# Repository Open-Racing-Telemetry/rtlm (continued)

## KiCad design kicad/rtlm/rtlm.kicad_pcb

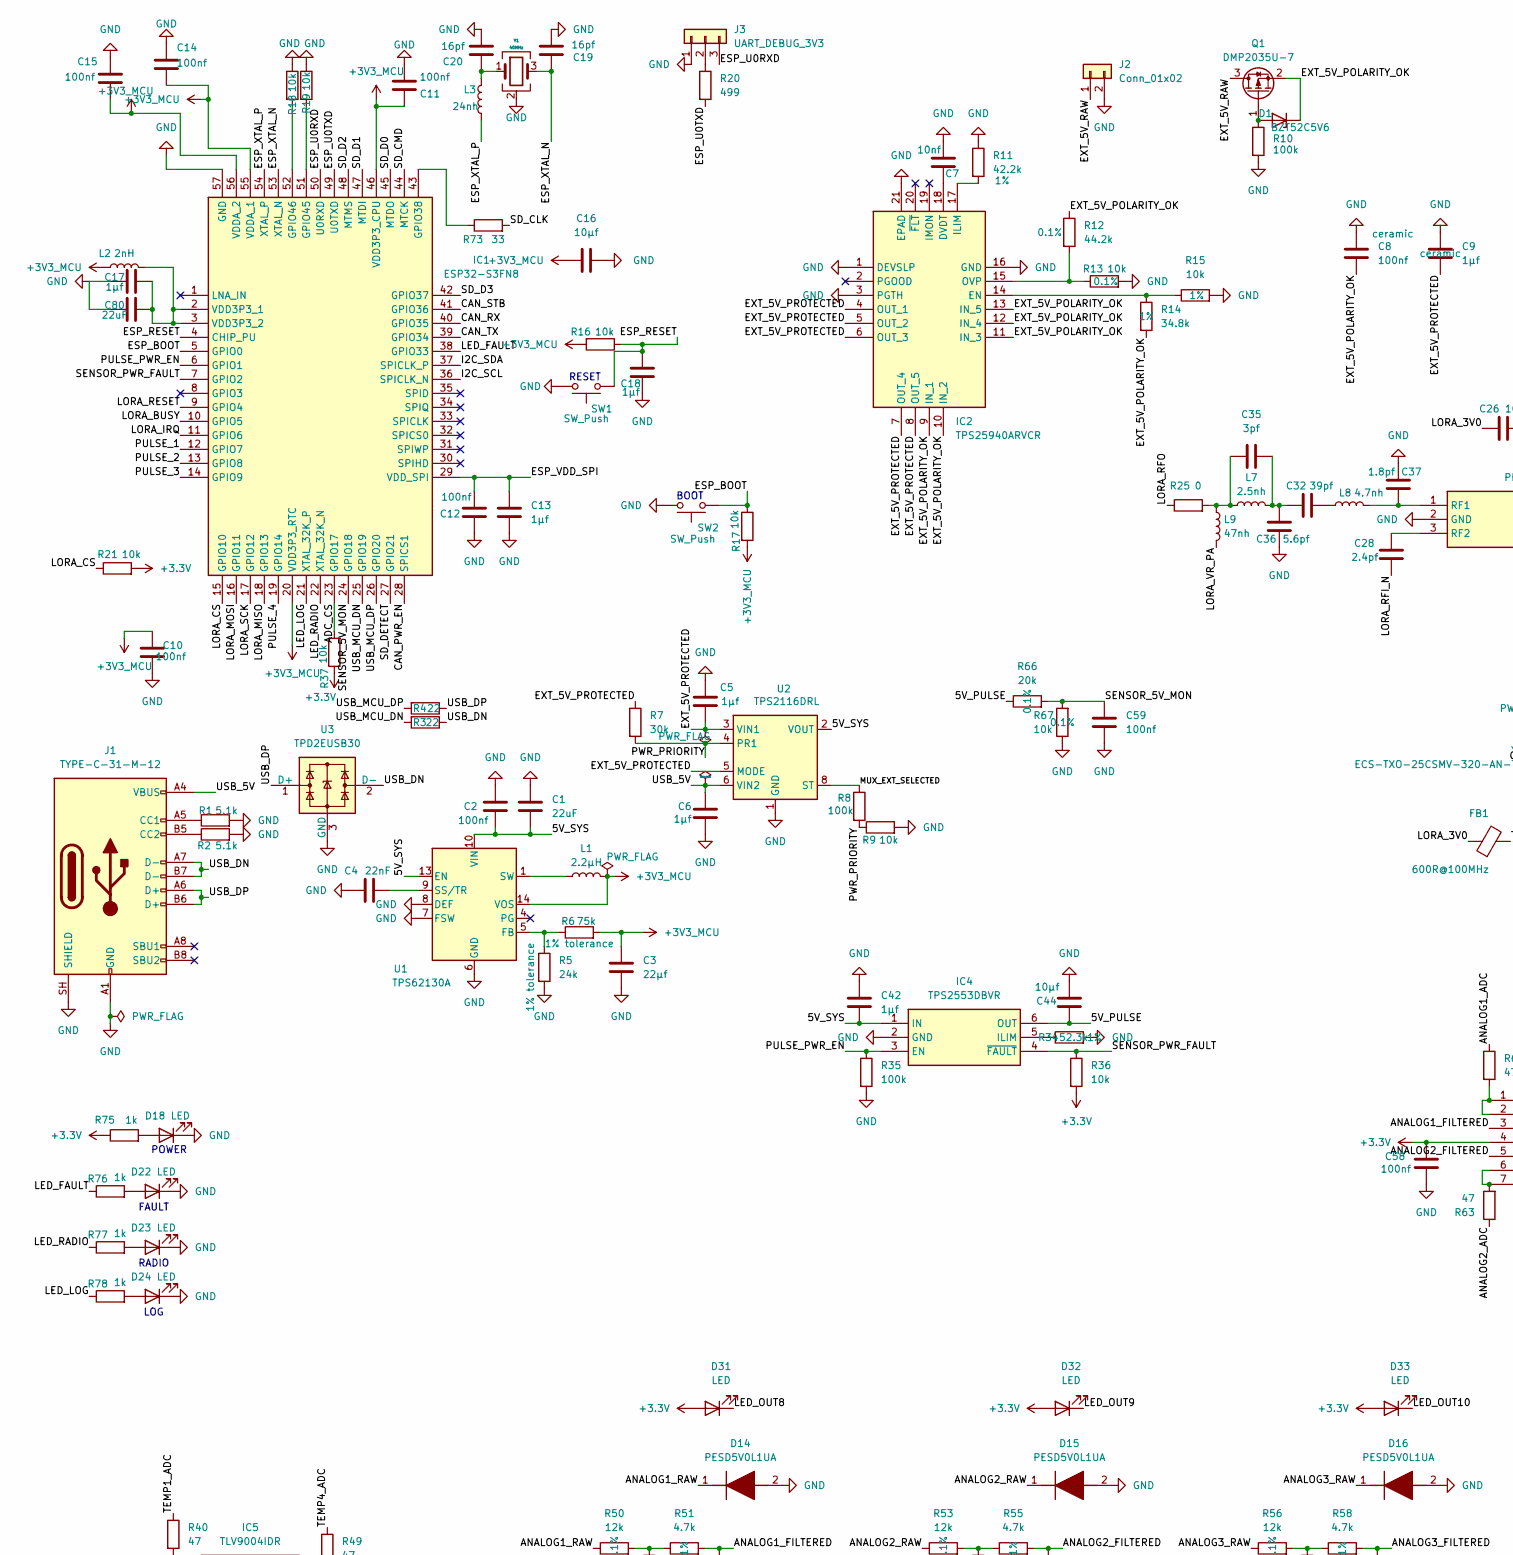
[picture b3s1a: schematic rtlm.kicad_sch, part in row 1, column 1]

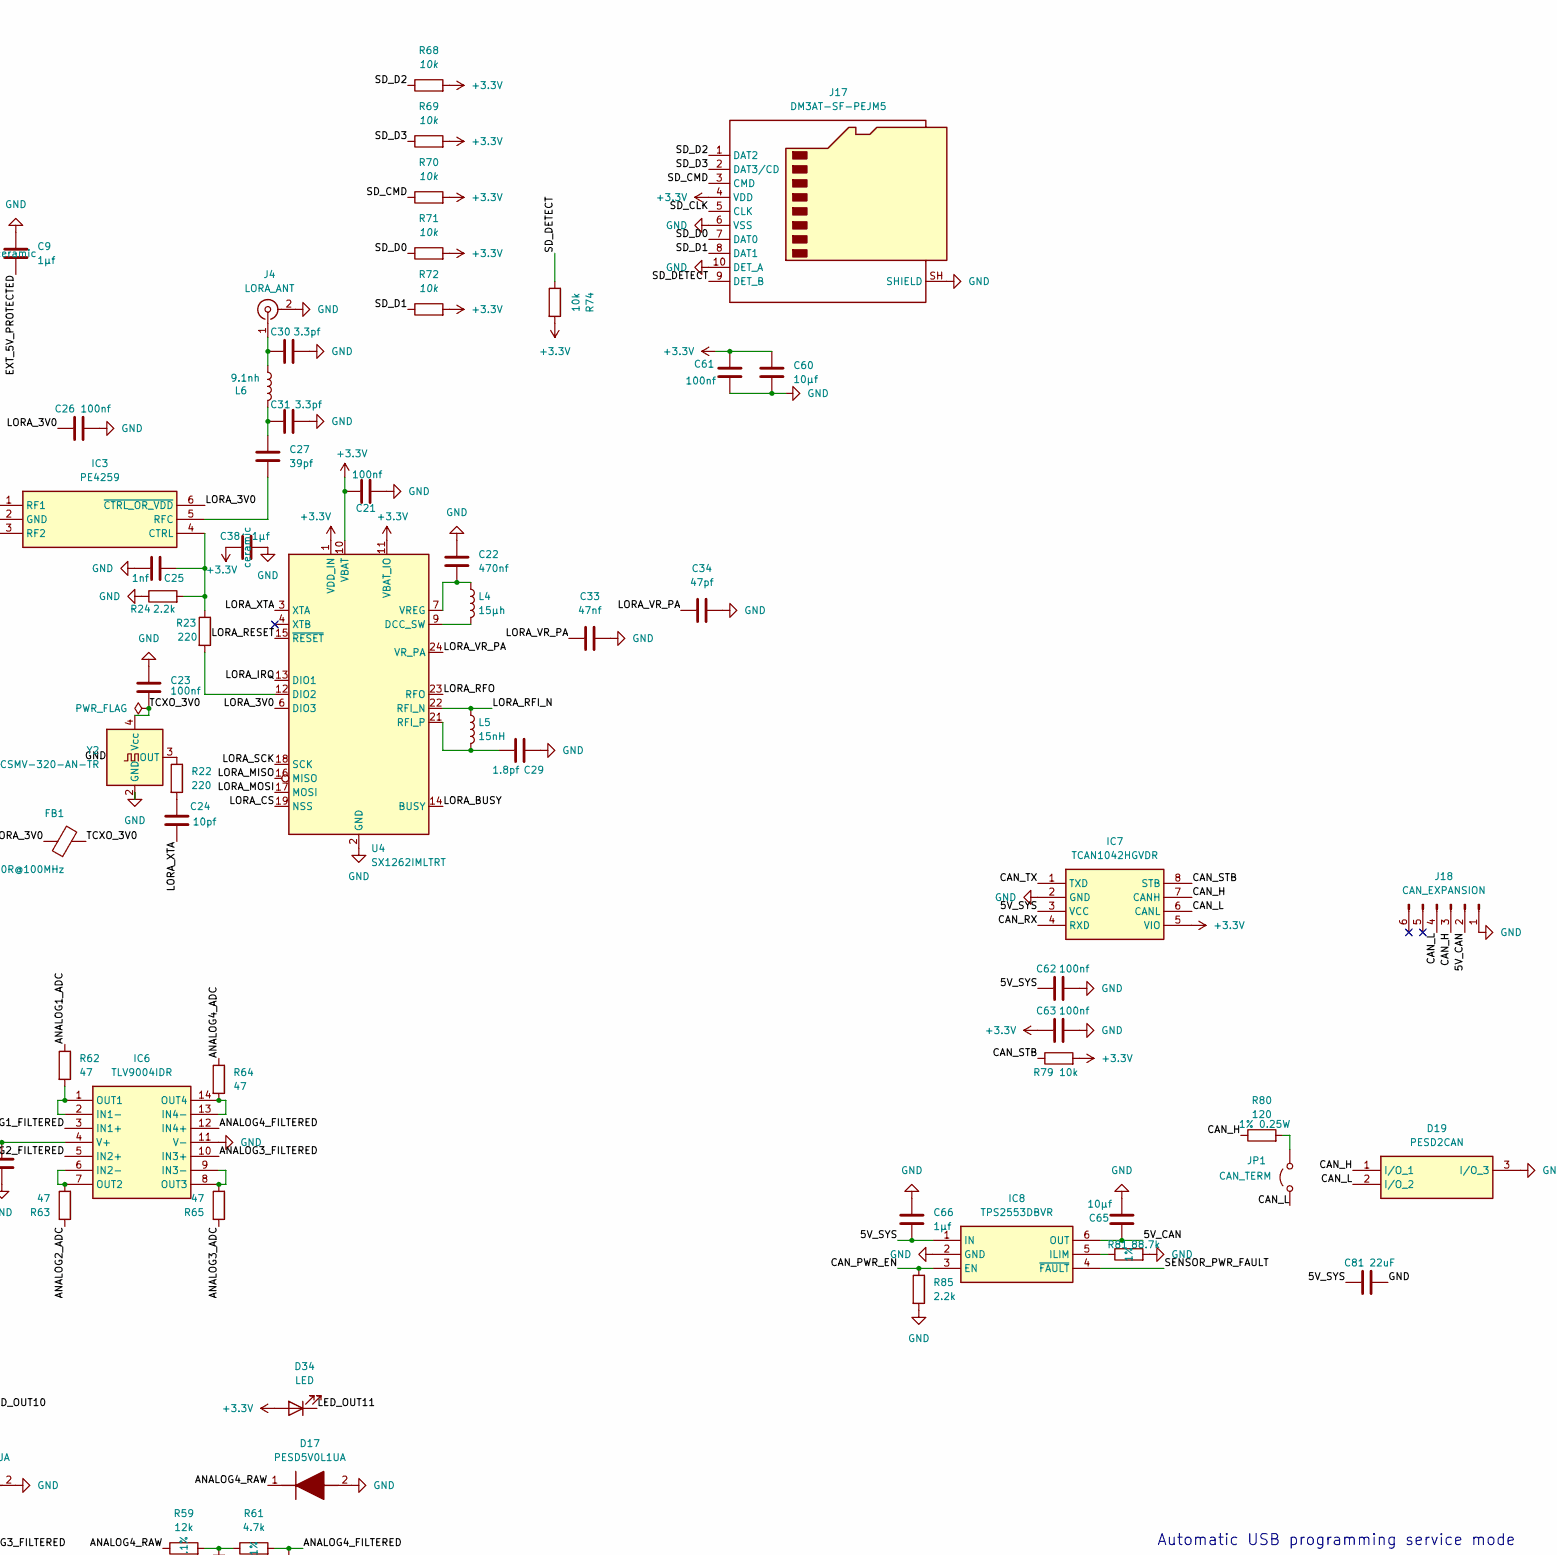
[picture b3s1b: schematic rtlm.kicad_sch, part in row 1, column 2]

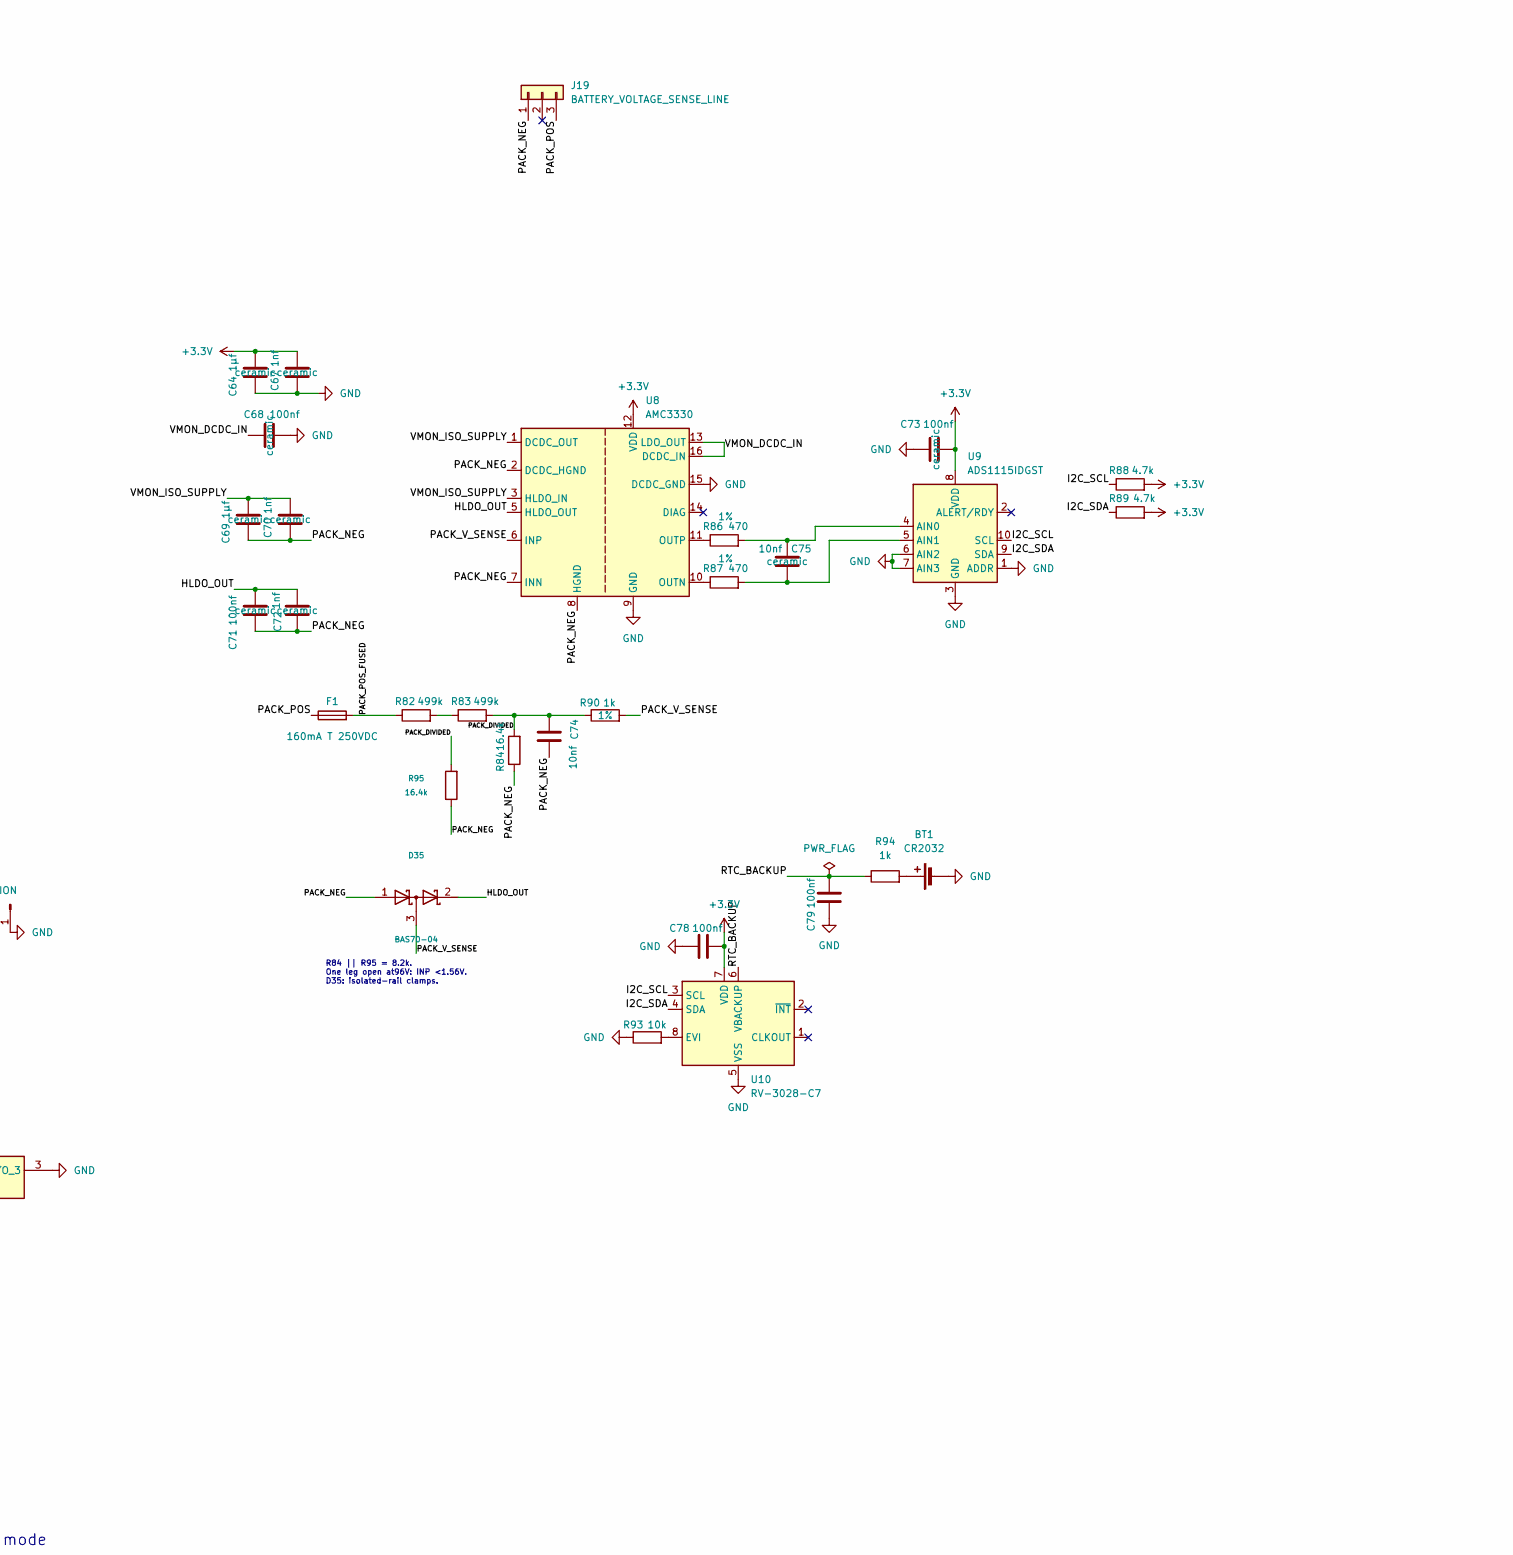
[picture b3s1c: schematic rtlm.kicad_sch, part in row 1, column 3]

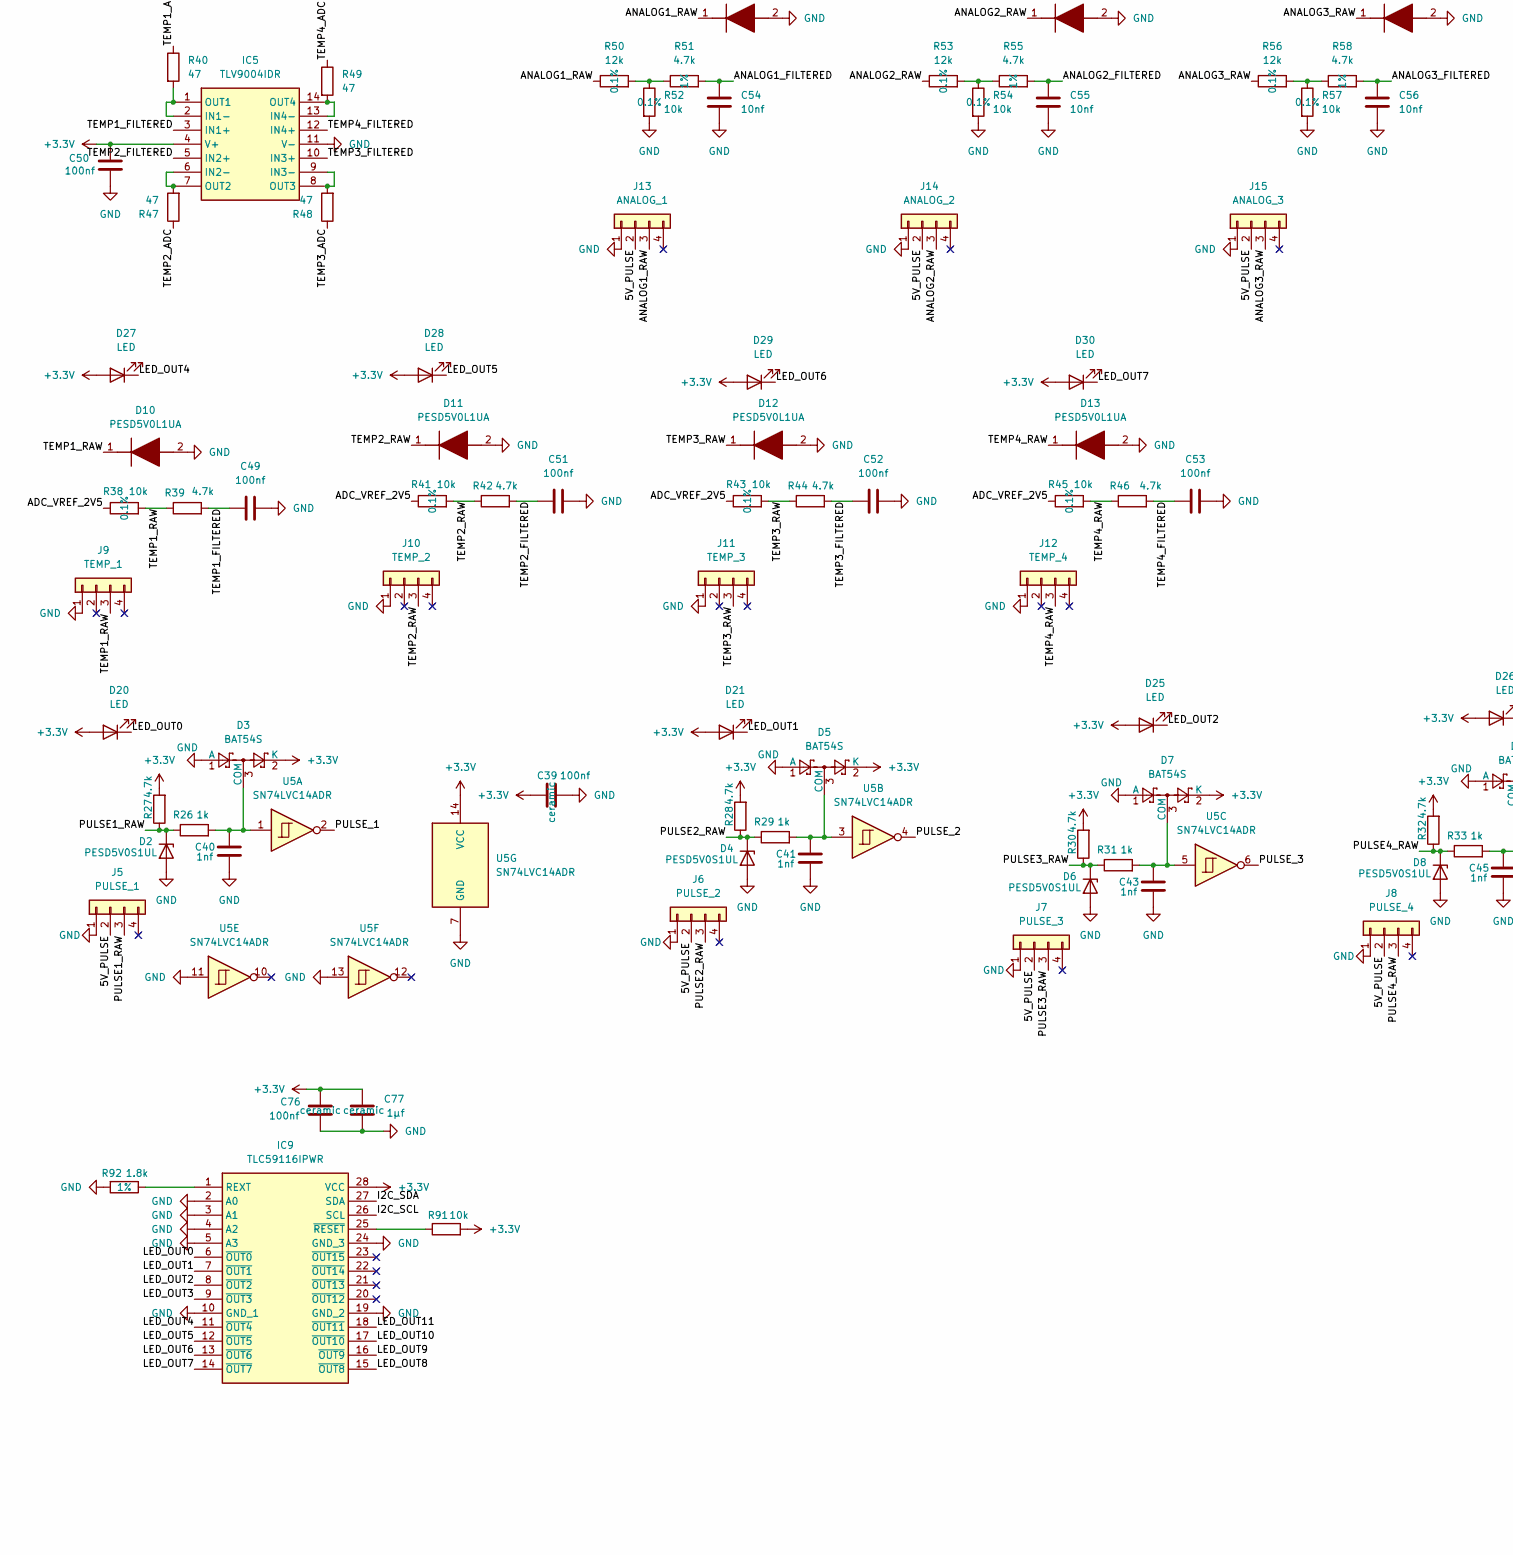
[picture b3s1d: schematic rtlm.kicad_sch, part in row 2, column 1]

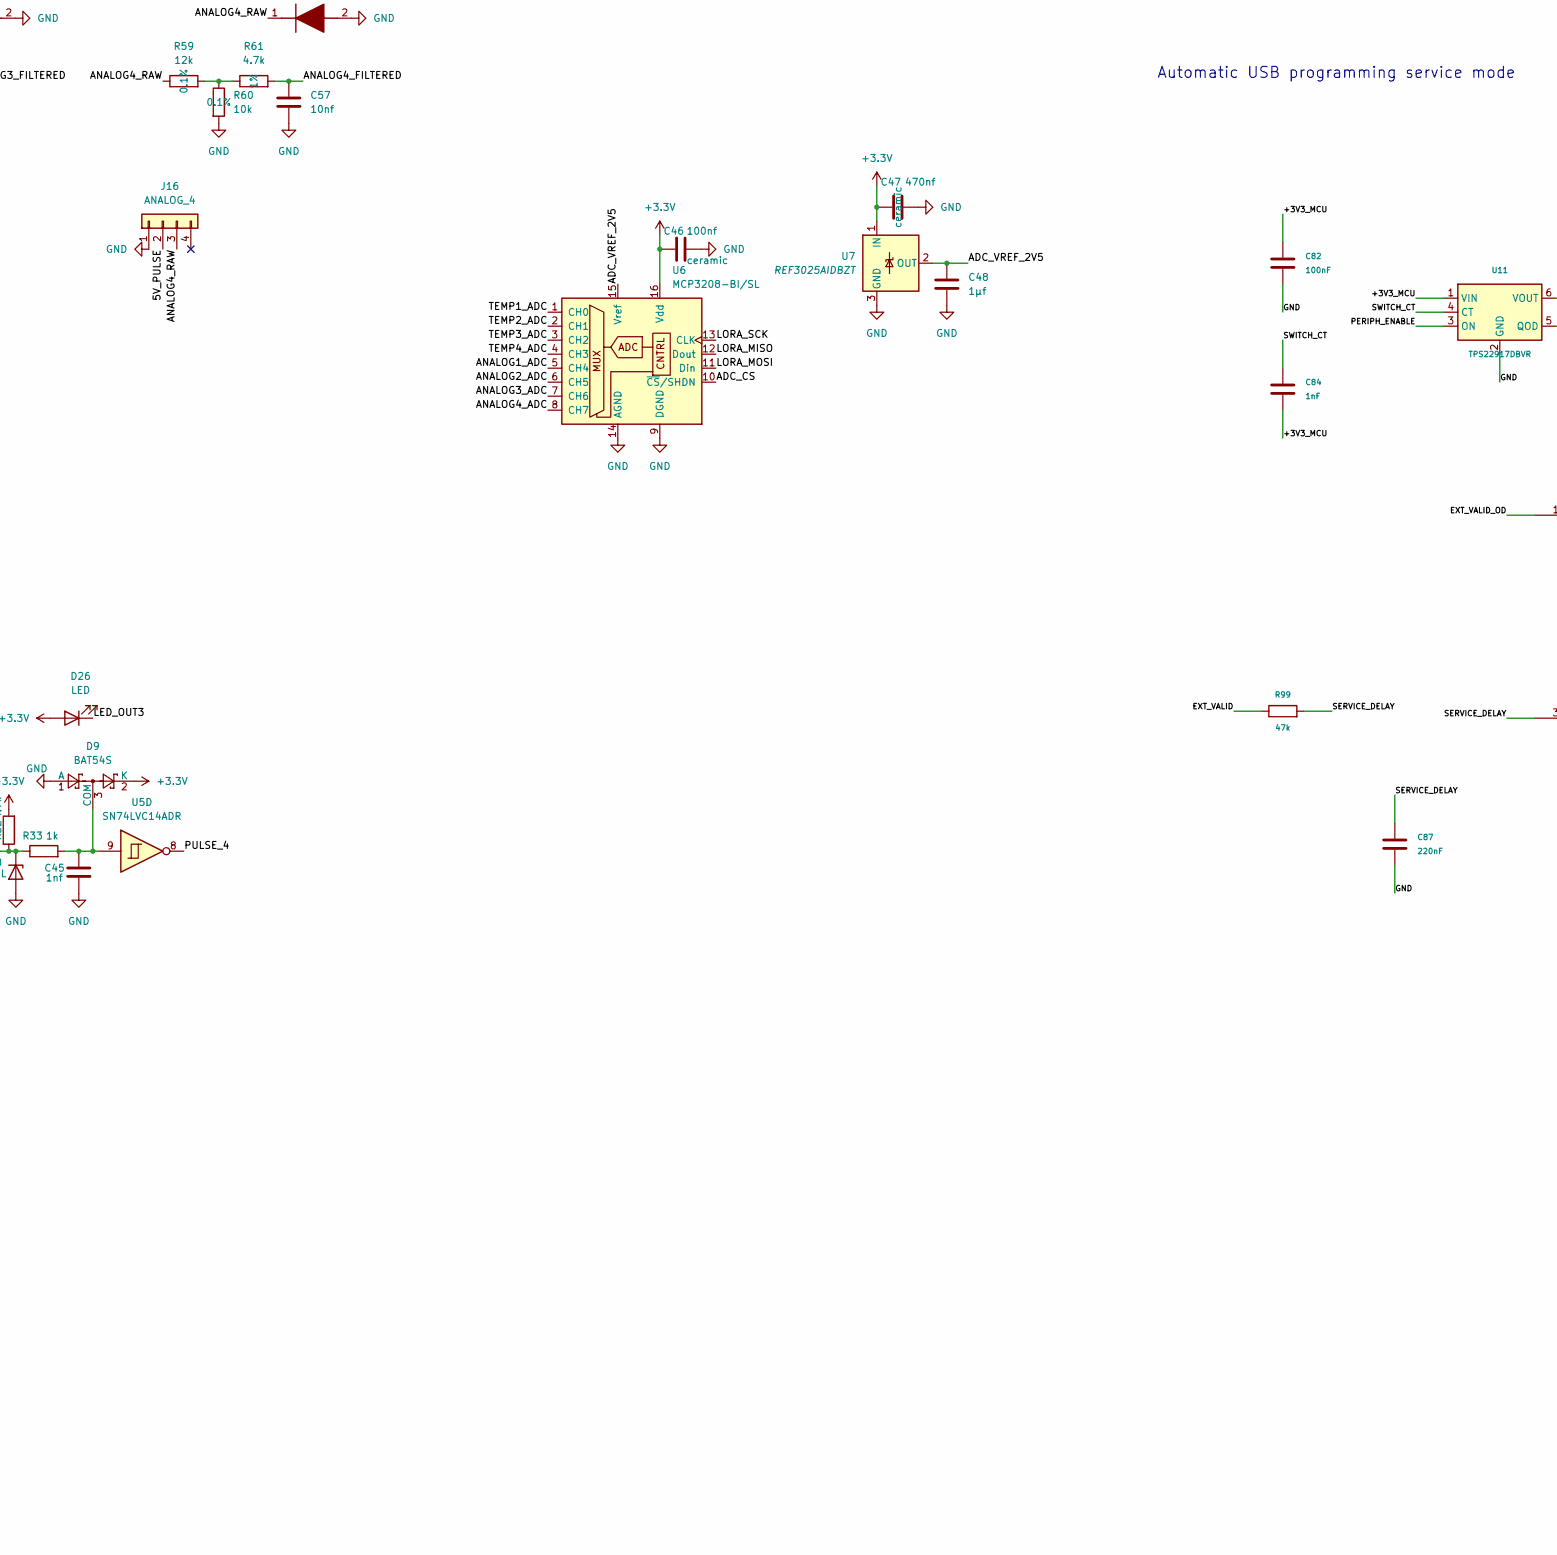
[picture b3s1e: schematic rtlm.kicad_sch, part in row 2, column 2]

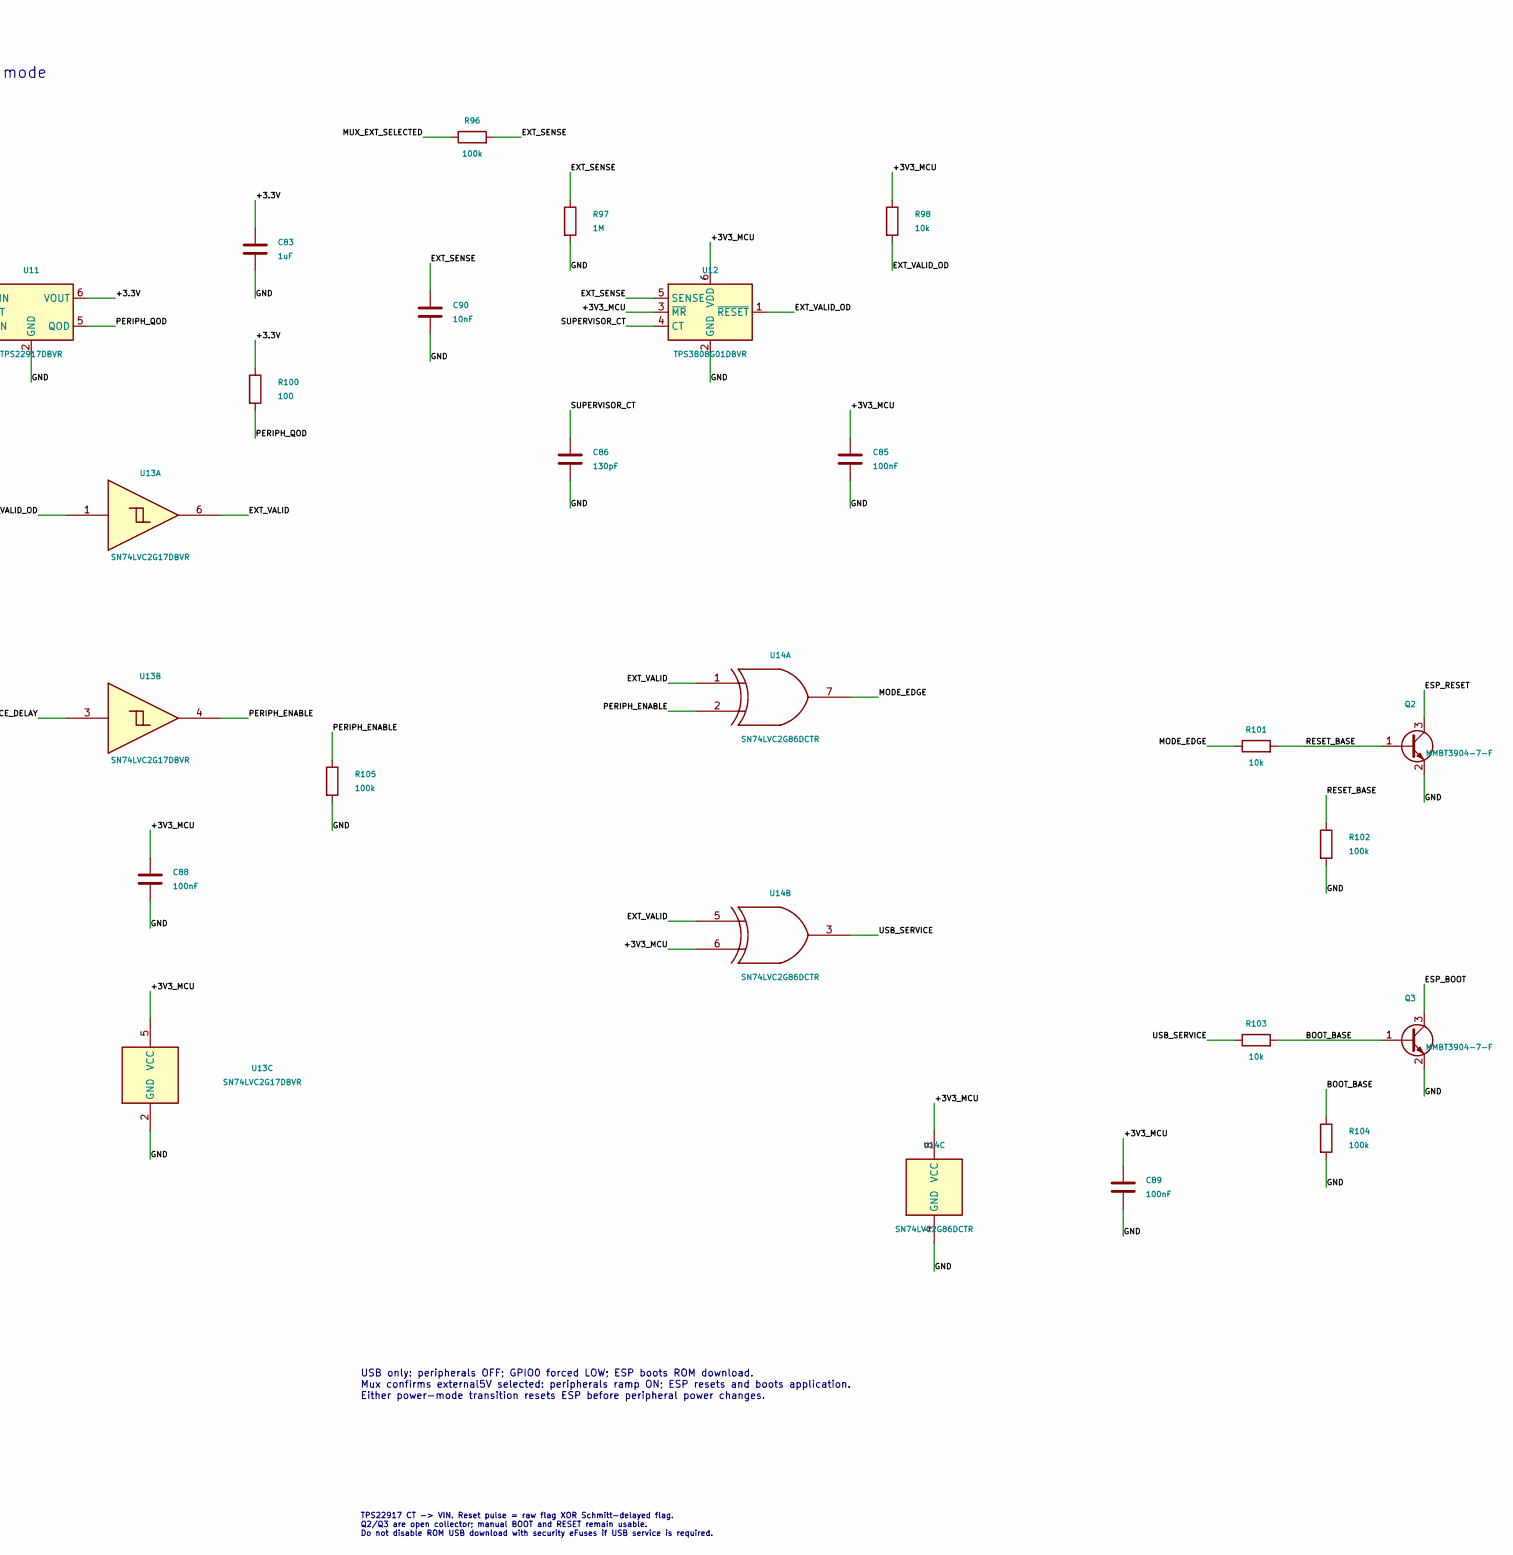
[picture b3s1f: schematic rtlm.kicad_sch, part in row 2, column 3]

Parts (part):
BT1: CR2032; BatteryHolder_Keystone_1060_1x2032; MPN 1060
C1, C80, C81: 22uF; C_0805_2012Metric; MPN GRM21BR61E226ME44L; LCSC Part Number C86816
C2, C8, C10, C11, C12, C14, C15, C39, C46, C49, C50, C51, C52, C53, C58, C59, C61, C62, C63, C68, C73, C76, C78, C79: 100nf; C_0603_1608Metric; MPN CC0603KRX7R9BB104; LCSC Part Number C14663
C3: 22µf; C_1206_3216Metric; MPN GRM31CR71A226KE15L; LCSC Part Number C91604
C4: 22nF; C_0603_1608Metric; MPN CC0603KRX7R9BB223; LCSC Part Number C106222
C5, C6, C9, C13, C17, C18, C38, C42, C48, C66, C69, C77: 1µf; C_0603_1608Metric; MPN CC0603KRX7R8BB105; LCSC Part Number C106858
C7, C54, C55, C56, C57, C75: 10nf; C_0603_1608Metric; MPN CC0603KRX7R9BB103; LCSC Part Number C100042
C16, C44, C60, C65: 10µf; C_0805_2012Metric; MPN GRM21BZ71E106KE15L; LCSC Part Number C237493
C19, C20: 16pf; C_0603_1608Metric; MPN GRM1885C1H160JA01D
C21, C23, C26: 100nf; C_0402_1005Metric; MPN CC0402KRX7R9BB104; LCSC Part Number C131394
C22: 470nf; C_0402_1005Metric; MPN CC0402KRX5R6BB474; LCSC Part Number C106255
C24: 10pf; C_0402_1005Metric; MPN GJM1555C1H100JB01D; LCSC Part Number C85874
C25: 1nf; C_0402_1005Metric; MPN CC0402JRNPO9BN102
C27, C32: 39pf; C_0402_1005Metric; MPN GJM1555C1H390JB01D
C28: 2.4pf; C_0402_1005Metric; MPN GJM1555C1H2R4BB01D
C29, C37: 1.8pf; C_0402_1005Metric; MPN GJM1555C1H1R8BB01D; LCSC Part Number C76902
C30, C31: 3.3pf; C_0402_1005Metric; MPN GJM1555C1H3R3BB01D; LCSC Part Number C76906
C33: 47nf; C_0402_1005Metric; MPN GRM155R71C473KA01D; LCSC Part Number C77012
C34: 47pf; C_0402_1005Metric; MPN GJM1555C1H470JB01D; LCSC Part Number C161322
C35: 3pf; C_0402_1005Metric; MPN GJM1555C1H3R0BB01D; LCSC Part Number C88891
C36: 5.6pf; C_0402_1005Metric; MPN GJM1555C1H5R6CB01D; LCSC Part Number C88895
C40, C41, C43, C45, C70: 1nf; C_0603_1608Metric; MPN CC0603JRNPO9BN102; LCSC Part Number C106246
C47: 470nf; C_0603_1608Metric; MPN CC0603KRX7R7BB474; LCSC Part Number C106851
C64: 1µf; C_1206_3216Metric; MPN CC1206KKX7R9BB105; LCSC Part Number C107185
C67, C72: 1nf; C_1206_3216Metric; MPN CC1206JRNPO9BN102; LCSC Part Number C113881
C71: 100nf; C_1206_3216Metric; MPN CC1206KRX7R9BB104; LCSC Part Number C82601
C74: 10nf; C_0603_1608Metric; MPN CC0603KRX7R0BB103; LCSC Part Number C107059
C82, C85, C88, C89: 100nF; C_0603_1608Metric; MPN CC0603KRX7R9BB104; LCSC Part Number C14663
C83: 1uF; C_0603_1608Metric; MPN CC0603KRX7R8BB105; LCSC Part Number C106858
C84: 1nF; C_0603_1608Metric; MPN CC0603JRNPO9BN102; LCSC Part Number C106246
C86: 130pF; C_0603_1608Metric; MPN CC0603JRNPO9BN131
C87: 220nF; C_0603_1608Metric; MPN CC0603KRX7R9BB224; LCSC Part Number C107083
C90: 10nF; C_0603_1608Metric; MPN CC0603KRX7R9BB103; LCSC Part Number C100042
D1: BZT52C5V6; D_SOD-123; MPN BZT52C5V6-7-F; LCSC Part Number C397930
D2, D4, D6, D8: PESD5V0S1UL; D_SOD-882; MPN PESD5V0S1UL,315; LCSC Part Number C85402
D3, D5, D7, D9: BAT54S; SOT-23; MPN BAT54S,215; LCSC Part Number C47546
D10, D11, D12, D13, D14, D15, D16, D17: PESD5V0L1UA; D_SOD-323; Manufacturer_Part_Number PESD5V0L1UA; Mouser Part Number N/A
D18, D20, D21, D22, D23, D24, D25, D26, D27, D28, D29, D30, D31, D32, D33, D34: LED; LED_0603_1608Metric; MPN APT1608SGC; LCSC Part Number C5875754
D19: PESD2CAN; SOT-23; Manufacturer_Part_Number PESD2CAN; LCSC Part Number C284078
D35: BAS70-04; SOT-23; MPN BAS70-04,215
F1: 160mA T 250VDC; UMT-H; MPN 3403.0266.23; LCSC Part Number C3159235
FB1: 600R@100MHz; L_0603_1608Metric; MPN BLM18AG601SN1D; LCSC Part Number C19330
IC1: ESP32-S3FN8; ESP32_S3_QFN56_EP_Windowed; Manufacturer_Part_Number ESP32-S3FN8; Mouser Part Number 356-ESP32-S3FN8
IC2: TPS25940ARVCR; Texas_RVC0020A_WQFN-20-1EP_3x4mm_P0.5mm_EP1.6x2.6mm; Manufacturer_Part_Number TPS25940ARVCR; Mouser Part Number 595-TPS25940ARVCR
IC3: PE4259; SOT65P210X110-6N; Manufacturer_Part_Number PE4259-63; Mouser Part Number N/A
IC4, IC8: TPS2553DBVR; SOT-23-6; Manufacturer_Part_Number TPS2553DBVR; Mouser Part Number 595-TPS2553DBVR
IC5, IC6: TLV9004IDR; SOIC127P600X175-14N; Manufacturer_Part_Number TLV9004IDR; Mouser Part Number 595-TLV9004IDR
IC7: TCAN1042HGVDR; SOIC-8_3.9x4.9mm_P1.27mm; Manufacturer_Part_Number TCAN1042HGVDR; Mouser Part Number 595-TCAN1042HGVDR
IC9: TLC59116IPWR; SOP65P640X120-28N; Manufacturer_Part_Number TLC59116IPWR; Mouser Part Number 595-TLC59116IPWR
J1: TYPE-C-31-M-12; USB_C_HRO_TYPE_C_31_M_12_OEM_20201208; MPN TYPE-C-31-M-12; LCSC Part Number C165948
J2: Conn_01x02; Molex_Micro-Fit_3.0_43650-0200_1x02_P3.00mm_Horizontal; MPN 436500200; LCSC Part Number C192562
J3: UART_DEBUG_3V3; PinHeader_1x03_P2.54mm_Vertical; MPN TSW-103-07-G-S; LCSC Part Number C3335811
J4: LORA_ANT; U.FL_Hirose_U.FL-R-SMT-1_Vertical; MPN U.FL-R-SMT-1(10); LCSC Part Number C88373
J5: PULSE_1; Molex_Micro-Fit_3.0_43045-0400_2x02_P3.00mm_Horizontal; MPN 430450400; LCSC Part Number C122413
J6: PULSE_2; Molex_Micro-Fit_3.0_43045-0400_2x02_P3.00mm_Horizontal; MPN 430450400; LCSC Part Number C122413
J7: PULSE_3; Molex_Micro-Fit_3.0_43045-0400_2x02_P3.00mm_Horizontal; MPN 430450400; LCSC Part Number C122413
J8: PULSE_4; Molex_Micro-Fit_3.0_43045-0400_2x02_P3.00mm_Horizontal; MPN 430450400; LCSC Part Number C122413
J9: TEMP_1; Molex_Micro-Fit_3.0_43045-0400_2x02_P3.00mm_Horizontal; MPN 430450400; LCSC Part Number C122413
J10: TEMP_2; Molex_Micro-Fit_3.0_43045-0400_2x02_P3.00mm_Horizontal; MPN 430450400; LCSC Part Number C122413
J11: TEMP_3; Molex_Micro-Fit_3.0_43045-0400_2x02_P3.00mm_Horizontal; MPN 430450400; LCSC Part Number C122413
J12: TEMP_4; Molex_Micro-Fit_3.0_43045-0400_2x02_P3.00mm_Horizontal; MPN 430450400; LCSC Part Number C122413
J13: ANALOG_1; Molex_Micro-Fit_3.0_43045-0400_2x02_P3.00mm_Horizontal; MPN 430450400; LCSC Part Number C122413
J14: ANALOG_2; Molex_Micro-Fit_3.0_43045-0400_2x02_P3.00mm_Horizontal; MPN 430450400; LCSC Part Number C122413
J15: ANALOG_3; Molex_Micro-Fit_3.0_43045-0400_2x02_P3.00mm_Horizontal; MPN 430450400; LCSC Part Number C122413
J16: ANALOG_4; Molex_Micro-Fit_3.0_43045-0400_2x02_P3.00mm_Horizontal; MPN 430450400; LCSC Part Number C122413
J17: DM3AT-SF-PEJM5; microSD_HC_Hirose_DM3AT-SF-PEJM5; MPN DM3AT-SF-PEJM5(40); LCSC Part Number C597971
J18: CAN_EXPANSION; Molex_Micro-Fit_3.0_43045-0600_2x03_P3.00mm_Horizontal; MPN 430450600; LCSC Part Number C127367
J19: BATTERY_VOLTAGE_SENSE_LINE; Molex_Micro-Fit_3.0_43650-0300_1x03_P3.00mm_Horizontal; MPN 436500300; LCSC Part Number C503478
JP1: CAN_TERM; PinHeader_1x02_P2.54mm_Vertical; MPN TSW-102-07-G-S; LCSC Part Number C7402729
L1: 2.2µH; L_Coilcraft_XxL4020; MPN XAL4020-222MEC; LCSC Part Number C3151182
L2: 2nH; L_0402_1005Metric; MPN 0402HP-2N0XJRW
L3: 24nh; L_0402_1005Metric; MPN 0402HP-24NXJRW
L4: 15µh; L_0805_2012Metric; MPN MLZ2012M150WT000; LCSC Part Number C383402
L5: 15nH; L_0402_1005Metric; MPN LQW15AN15NH00D; LCSC Part Number C91621
L6: 9.1nh; L_0402_1005Metric; MPN LQW15AN9N1H00D
L7: 2.5nh; L_0402_1005Metric; MPN LQW15AN2N5C00D; LCSC Part Number C703121
L8: 4.7nh; L_0402_1005Metric; MPN LQW15AN4N7C00D; LCSC Part Number C167480
L9: 47nh; L_0402_1005Metric; MPN 0402HP-47NXJRW
Q1: DMP2035U-7; SOT-23; MPN DMP2035U-7; LCSC Part Number C110499
Q2, Q3: MMBT3904-7-F; SOT-23; MPN MMBT3904-7-F; LCSC Part Number C94514
R1, R2: 5.1k; R_0603_1608Metric; MPN RC0603FR-075K1L; LCSC Part Number C105580
R3, R4: 22; R_0603_1608Metric; MPN RC0603FR-0722RL; LCSC Part Number C107701
R5: 24k; R_0603_1608Metric; MPN RC0603FR-0724KL; LCSC Part Number C137760
R6: 75k; R_0603_1608Metric; MPN RC0603FR-0775KL; LCSC Part Number C114636
R7: 30k; R_0603_1608Metric; MPN RC0603FR-0730KL; LCSC Part Number C100001
R8, R10, R35, R96, R102, R104, R105: 100k; R_0603_1608Metric; MPN RC0603FR-07100KL; LCSC Part Number C14675
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
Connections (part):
+3.3V: C21.1, C38.1, C39.1, C46.1, C47.1, C50.1, C58.1, C60.1, C61.1, C63.1, C64.2, C67.2, C73.2, C76.1, C77.1, C78.2, C83.1, D3.2 (K), D5.2 (K), D7.2 (K), D9.2 (K), D20.2 (A), D21.2 (A), D25.2 (A), D26.2 (A), D27.2 (A), D28.2 (A), D29.2 (A), D30.2 (A), D31.2 (A), D32.2 (A), D33.2 (A), D34.2 (A), IC5.4 (V+), IC6.4 (V+), IC7.5 (VIO), IC9.28 (VCC), J17.4 (VDD), R21.2, R27.2, R28.2, R30.2, R32.2, R36.2, R37.1, R68.2, R69.2, R70.2, R71.2, R72.2, R74.2, R75.1, R79.2, R88.2, R89.2, R91.2, R100.1, U4.1 (VDD_IN), U4.10 (VBAT), U4.11 (VBAT_IO), U5.14 (VCC), U6.16 (Vdd), U7.1 (IN), U8.12 (VDD), U9.8 (VDD), U10.7 (VDD), U11.6 (VOUT)
+3V3_MCU: C3.1, C10.2, C11.2, C14.2, C15.2, C16.1, C82.1, C84.2, C85.1, C88.1, C89.1, IC1.20 (VDD3P3_RTC), IC1.46 (VDD3P3_CPU), IC1.55 (VDDA_1), IC1.56 (VDDA_2), L1.2, L2.1, R6.2, R16.2, R17.2, R98.1, U1.14 (VOS), U11.1 (VIN), U12.3 (~MR), U12.6 (VDD), U13.5 (VCC), U14.6, U14.8 (VCC)
/5V_CAN: C65.2, IC8.6 (OUT), J18.2
/5V_PULSE: C44.2, IC4.6 (OUT), J5.2, J6.2, J7.2, J8.2, J13.2, J14.2, J15.2, J16.2, R66.1
/5V_SYS: C1.2, C2.2, C42.2, C62.1, C66.2, C81.1, IC4.1 (IN), IC7.3 (VCC), IC8.1 (IN), U1.10 (VIN), U1.11 (VIN), U1.12 (VIN), U1.13 (EN), U2.2 (VOUT), U2.7 (VOUT)
/ADC_CS: IC1.23 (GPIO17), R37.2, U6.10 (~CS/SHDN)
/ADC_VREF_2V5: C48.1, R38.1, R41.1, R43.1, R45.1, U6.15 (Vref), U7.2 (OUT)
/ANALOG1_ADC: R62.1, U6.5 (CH4)
/ANALOG1_FILTERED: C54.1, IC6.3 (IN1+), R51.2
/ANALOG1_RAW: D14.1 (K), J13.3, R50.1
/ANALOG2_ADC: R63.1, U6.6 (CH5)
/ANALOG2_FILTERED: C55.1, IC6.5 (IN2+), R55.2
/ANALOG2_RAW: D15.1 (K), J14.3, R53.1
/ANALOG3_ADC: R65.1, U6.7 (CH6)
/ANALOG3_FILTERED: C56.1, IC6.10 (IN3+), R58.2
/ANALOG3_RAW: D16.1 (K), J15.3, R56.1
/ANALOG4_ADC: R64.1, U6.8 (CH7)
/ANALOG4_FILTERED: C57.1, IC6.12 (IN4+), R61.2
/ANALOG4_RAW: D17.1 (K), J16.3, R59.1
/BOOT_BASE: Q3.1 (B), R103.2, R104.1
/CAN_H: D19.1 (I/O_1), IC7.7 (CANH), J18.3, R80.1
/CAN_L: D19.2 (I/O_2), IC7.6 (CANL), J18.4, JP1.1 (A)
/CAN_PWR_EN: IC1.28 (SPICS1), IC8.3 (EN), R85.1
/CAN_RX: IC1.40 (GPIO35), IC7.4 (RXD)
/CAN_STB: IC1.41 (GPIO36), IC7.8 (STB), R79.1
/CAN_TX: IC1.39 (GPIO34), IC7.1 (TXD)
/ESP_BOOT: IC1.5 (GPIO0), Q3.3 (C), R17.1, SW2.1
/ESP_RESET: C18.2, IC1.4 (CHIP_PU), Q2.3 (C), R16.1, SW1.1
/ESP_U0RXD: IC1.50 (U0RXD), J3.3
/ESP_U0TXD: IC1.49 (U0TXD), R20.2
/ESP_VDD_SPI: C12.1, C13.1, IC1.29 (VDD_SPI)
/ESP_XTAL_N: C19.2, IC1.53 (XTAL_N), Y1.3
/ESP_XTAL_P: IC1.54 (XTAL_P), L3.1
/EXT_5V_POLARITY_OK: C8.2, D1.1 (K), IC2.9 (IN_1), IC2.10 (IN_2), IC2.11 (IN_3), IC2.12 (IN_4), IC2.13 (IN_5), Q1.2 (S), R12.1, R14.2
/EXT_5V_PROTECTED: C5.2, C9.2, IC2.4 (OUT_1), IC2.5 (OUT_2), IC2.6 (OUT_3), IC2.7 (OUT_4), IC2.8 (OUT_5), R7.1, U2.3 (VIN1), U2.5 (MODE)
/EXT_5V_RAW: J2.1, Q1.3 (D)
/EXT_SENSE: C90.1, R96.2, R97.1, U12.5 (SENSE)
/EXT_VALID: R99.1, U13.6, U14.1, U14.5
/EXT_VALID_OD: R98.2, U12.1 (~RESET), U13.1
/HLDO_OUT: C71.2, C72.2, D35.2 (K), U8.5 (HLDO_OUT)
/I2C_SCL: IC1.36 (SPICLK_N), IC9.26 (SCL), R88.1, U9.10 (SCL), U10.3 (SCL)
/I2C_SDA: IC1.37 (SPICLK_P), IC9.27 (SDA), R89.1, U9.9 (SDA), U10.4 (SDA)
/LED_FAULT: IC1.38 (GPIO33), R76.1
/LED_LOG: IC1.21 (XTAL_32K_P), R78.1
/LED_OUT0: D20.1 (K), IC9.6 (~OUT0)
/LED_OUT1: D21.1 (K), IC9.7 (~OUT1)
/LED_OUT2: D25.1 (K), IC9.8 (~OUT2)
/LED_OUT3: D26.1 (K), IC9.9 (~OUT3)
/LED_OUT4: D27.1 (K), IC9.11 (~OUT4)
/LED_OUT5: D28.1 (K), IC9.12 (~OUT5)
/LED_OUT6: D29.1 (K), IC9.13 (~OUT6)
/LED_OUT7: D30.1 (K), IC9.14 (~OUT7)
/LED_OUT8: D31.1 (K), IC9.15 (~OUT8)
/LED_OUT9: D32.1 (K), IC9.16 (~OUT9)
/LED_OUT10: D33.1 (K), IC9.17 (~OUT10)
/LED_OUT11: D34.1 (K), IC9.18 (~OUT11)
/LED_RADIO: IC1.22 (XTAL_32K_N), R77.1
/LORA_3V0: C26.2, FB1.1, IC3.6 (~CTRL_OR_VDD), U4.6 (DIO3)
/LORA_BUSY: IC1.10 (GPIO5), U4.14 (BUSY)
/LORA_CS: IC1.15 (GPIO10), R21.1, U4.19 (NSS)
/LORA_IRQ: IC1.11 (GPIO6), U4.13 (DIO1)
/LORA_MISO: IC1.18 (GPIO13), U4.16 (MISO), U6.12 (Dout)
/LORA_MOSI: IC1.16 (GPIO11), U4.17 (MOSI), U6.11 (Din)
/LORA_RESET: IC1.9 (GPIO4), U4.15 (~RESET)
/LORA_RFI_N: C28.2, L5.1, U4.22 (RFI_N)
/LORA_RFO: R25.1, U4.23 (RFO)
/LORA_SCK: IC1.17 (GPIO12), U4.18 (SCK), U6.13 (CLK)
/LORA_VR_PA: C33.1, C34.1, L9.2, U4.24 (VR_PA)
/LORA_XTA: C24.2, U4.3 (XTA)
/MODE_EDGE: R101.1, U14.7
/MUX_EXT_SELECTED: R8.1, R96.1, U2.8 (ST)
/PACK_DIVIDED: C74.1, R83.2, R84.2, R90.1, R95.2
/PACK_NEG: C69.1, C70.1, C71.1, C72.1, C74.2, D35.1 (A), J19.1, R84.1, R95.1, U8.2 (DCDC_HGND), U8.7 (INN), U8.8 (HGND)
/PACK_POS: F1.1, J19.3
/PACK_POS_FUSED: F1.2, R82.1
/PACK_V_SENSE: D35.3 (common), R90.2, U8.6 (INP)
/PERIPH_ENABLE: R105.1, U11.3 (ON), U13.4, U14.2
/PERIPH_QOD: R100.2, U11.5 (QOD)
/PULSE1_RAW: D2.1 (K), J5.3, R26.1, R27.1
/PULSE2_RAW: D4.1 (K), J6.3, R28.1, R29.1
/PULSE3_RAW: D6.1 (K), J7.3, R30.1, R31.1
/PULSE4_RAW: D8.1 (K), J8.3, R32.1, R33.1
/PULSE_1: IC1.12 (GPIO7), U5.2
/PULSE_2: IC1.13 (GPIO8), U5.4
/PULSE_3: IC1.14 (GPIO9), U5.6
/PULSE_4: IC1.19 (GPIO14), U5.8
/PULSE_PWR_EN: IC1.6 (GPIO1), IC4.3 (EN), R35.1
/PWR_PRIORITY: R7.2, R8.2, R9.1, U2.4 (PR1)
/RESET_BASE: Q2.1 (B), R101.2, R102.1
/RTC_BACKUP: C79.2, R94.1, U10.6 (VBACKUP)
/SD_CLK: J17.5 (CLK), R73.2
/SD_CMD: IC1.44 (MTCK), J17.3 (CMD), R70.1
/SD_D0: IC1.45 (MTDO), J17.7 (DAT0), R71.1
/SD_D1: IC1.47 (MTDI), J17.8 (DAT1), R72.1
/SD_D2: IC1.48 (MTMS), J17.1 (DAT2), R68.1
/SD_D3: IC1.42 (GPIO37), J17.2 (DAT3/CD), R69.1
/SD_DETECT: IC1.27 (GPIO21), J17.9 (DET_B), R74.1
/SENSOR_5V_MON: C59.1, IC1.24 (GPIO18), R66.2, R67.2
/SENSOR_PWR_FAULT: IC1.7 (GPIO2), IC4.4 (~FAULT), IC8.4 (~FAULT), R36.1
/SERVICE_DELAY: C87.1, R99.2, U13.3
/SUPERVISOR_CT: C86.1, U12.4 (CT)
/SWITCH_CT: C84.1, U11.4 (CT)
/TCXO_3V0: C23.2, FB1.2, Y2.4 (Vcc)
/TEMP1_ADC: R40.1, U6.1 (CH0)
/TEMP1_FILTERED: C49.1, IC5.3 (IN1+), R39.2
/TEMP1_RAW: D10.1 (K), J9.3, R38.2, R39.1
/TEMP2_ADC: R47.1, U6.2 (CH1)
/TEMP2_FILTERED: C51.1, IC5.5 (IN2+), R42.2
/TEMP2_RAW: D11.1 (K), J10.3, R41.2, R42.1
/TEMP3_ADC: R48.1, U6.3 (CH2)
/TEMP3_FILTERED: C52.1, IC5.10 (IN3+), R44.2
/TEMP3_RAW: D12.1 (K), J11.3, R43.2, R44.1
/TEMP4_ADC: R49.1, U6.4 (CH3)
/TEMP4_FILTERED: C53.1, IC5.12 (IN4+), R46.2
/TEMP4_RAW: D13.1 (K), J12.3, R45.2, R46.1
/USB_5V: C6.1, J1.A4 (VBUS), J1.A9 (VBUS), J1.B4 (VBUS), J1.B9 (VBUS), U2.6 (VIN2)
/USB_DN: J1.A7 (D-), J1.B7 (D-), R3.1, U3.2 (D-)
/USB_DP: J1.A6 (D+), J1.B6 (D+), R4.1, U3.1 (D+)
/USB_MCU_DN: IC1.25 (GPIO19), R3.2
/USB_MCU_DP: IC1.26 (GPIO20), R4.2
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
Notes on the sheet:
RESET
FAULT
POWER
BOOT
RADIO
LOG
R84 || R95 = 8.2k. One leg open at96V: INP <1.56V. D35: isolated-rail clamps.
Automatic USB programming service mode
USB only: peripherals OFF; GPIO0 forced LOW; ESP boots ROM download. Mux confirms external5V selected: peripherals ramp ON; ESP resets and boots application. Either power-mode transition resets ESP before peripheral power changes.
TPS22917 CT -> VIN. Reset pulse = raw flag XOR Schmitt-delayed flag. Q2/Q3 are open collector; manual BOOT and RESET remain usable. Do not disable ROM USB download with security eFuses if USB service is required.

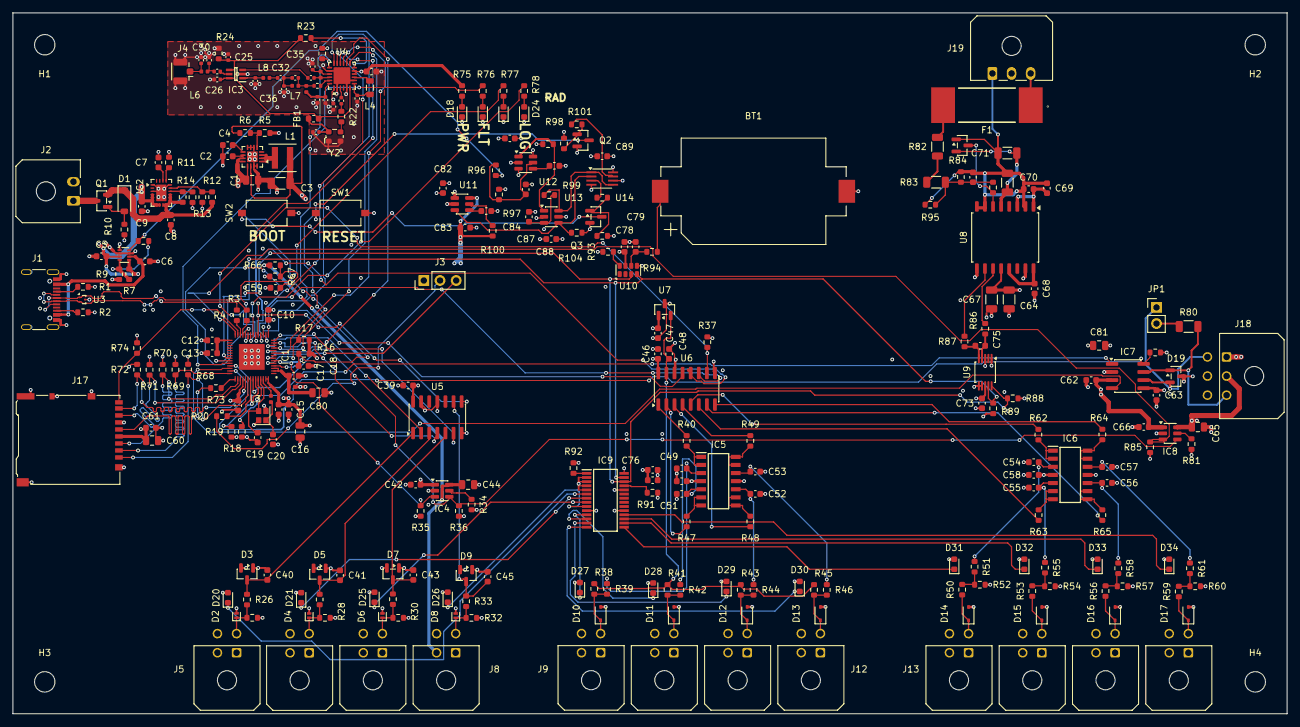
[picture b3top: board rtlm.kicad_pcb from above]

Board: 6 copper layers, 200.0 x 110.0 mm, 296 parts (0 on the bottom side), 187 nets.

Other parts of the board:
H1, H2, H3, H4: MountingHole_3.2mm_M3
